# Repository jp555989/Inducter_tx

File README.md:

# Inducter_tx
Project involved with designing transmitter for wireless power transfer circuit.
The input voltage is 12V DC, resonant frequency is set to 90kHz however it's possible to change it by switching values of RC circuit in CD4047.

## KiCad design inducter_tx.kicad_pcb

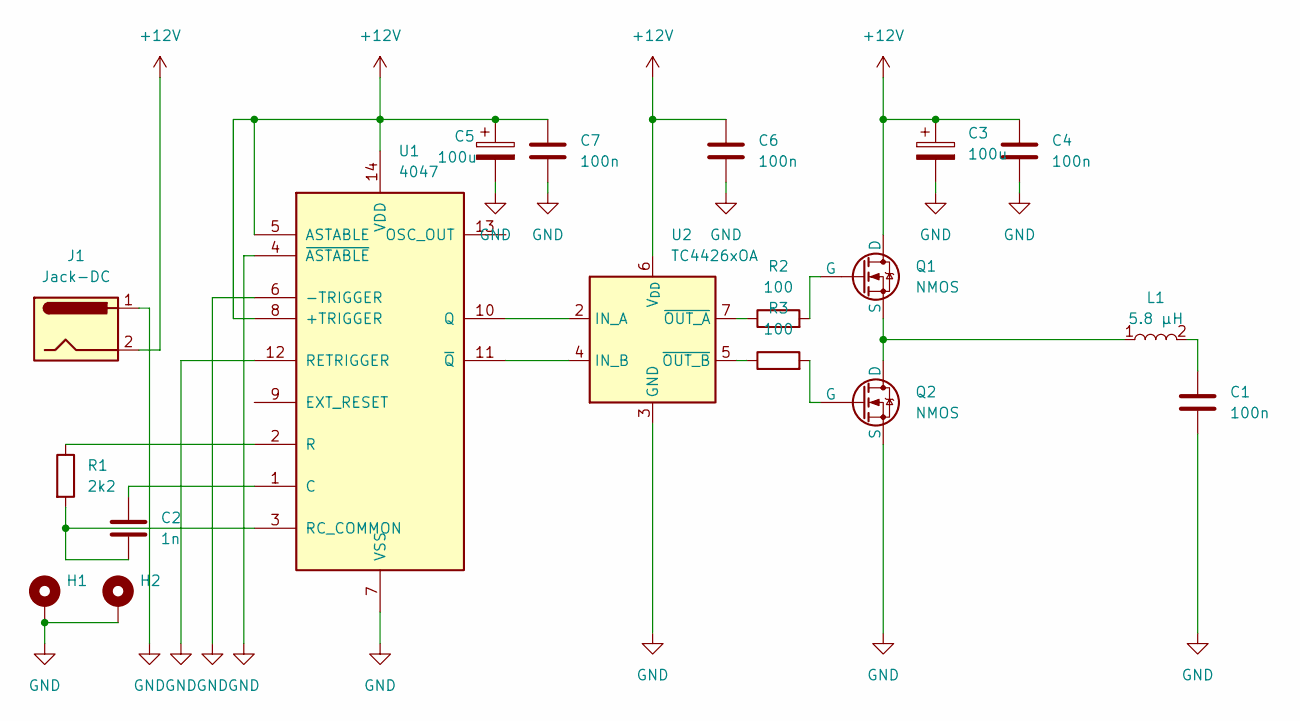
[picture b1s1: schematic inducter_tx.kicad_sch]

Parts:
C1, C4: 100n; C_1812_4532Metric_Pad1.57x3.40mm_HandSolder
C2: 1n; C_0805_2012Metric_Pad1.18x1.45mm_HandSolder
C3: 100u; C_Elec_6.3x5.4
C5: 100u; C_Elec_4x5.4
C6, C7: 100n; C_1206_3216Metric_Pad1.33x1.80mm_HandSolder
H1, H2: MountingHole_Pad; MountingHole_4.3mm_M4_DIN965_Pad
J1: Jack-DC; BarrelJack_CUI_PJ-063AH_Horizontal
L1: TX_760308101311; L_Wurth_WE-WPCC-TX_760308101311; Part Number 760308101311
Q1, Q2: NMOS; DPAK229P990X239-3Nlepszy
R1: 2k2; R_0805_2012Metric_Pad1.20x1.40mm_HandSolder
R2, R3: 100; R_0805_2012Metric_Pad1.20x1.40mm_HandSolder
U1: 4047; SOIC-14_3.9x8.7mm_P1.27mm
U2: TC4426xOA; SOIC-8_3.9x4.9mm_P1.27mm

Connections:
+12V: C3.1, C4.1, C5.1, C6.2, C7.2, J1.2, Q1.1 (D), U1.5 (ASTABLE), U1.8 (+TRIGGER), U1.14 (VDD), U2.6 (V_{DD})
GND: C1.2, C3.2, C4.2, C5.2, C6.1, C7.1, H1.1, H2.1, J1.1, Q2.3 (S), U1.4 (~ASTABLE), U1.6 (-TRIGGER), U1.7 (VSS), U1.12 (RETRIGGER), U2.3 (GND)
unnamed: C1.1, L1.2
unnamed: Q1.2 (G), R2.2
unnamed: L1.1, Q1.3 (S), Q2.1 (D)
unnamed: Q2.2 (G), R3.2
unnamed: C2.1, U1.1 (C)
unnamed: U1.10 (Q), U2.2 (IN_A)
unnamed: R1.1, U1.2 (R)
unnamed: C2.2, R1.2, U1.3 (RC_COMMON)
unnamed: U1.11 (~Q), U2.4 (IN_B)
unnamed: R2.1, U2.7 (~OUT_A)
unnamed: R3.1, U2.5 (~OUT_B)

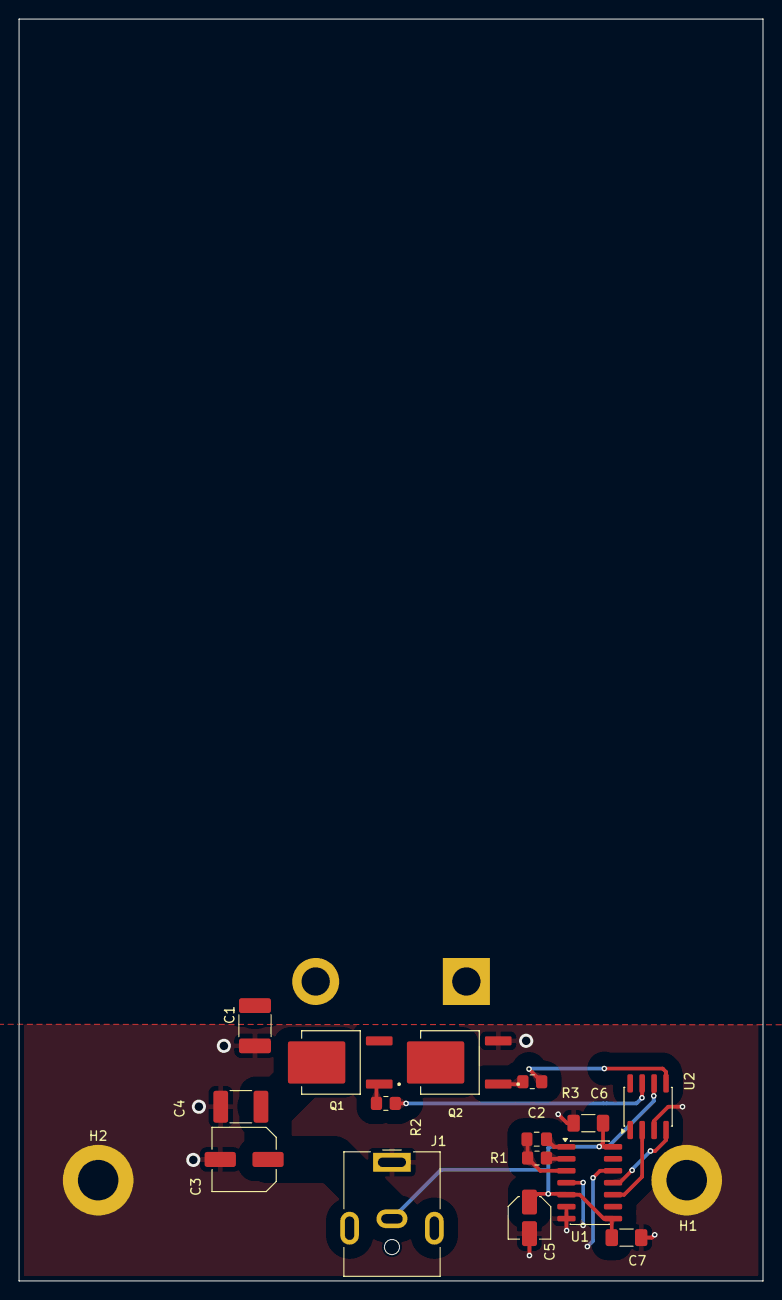
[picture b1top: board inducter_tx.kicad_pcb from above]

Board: 2 copper layers, 79.0 x 134.0 mm, 18 parts (1 on the bottom side), 13 nets.

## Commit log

2026-03-08 Update README with project images
    Added images to enhance project description.
2026-03-08 Update README with voltage and frequency information
    Added details about input voltage and resonant frequency.
2026-03-12 Add files via upload
    updated design
2026-03-12 Update README with additional images
    Added new images to the README for better visualization of the project.
